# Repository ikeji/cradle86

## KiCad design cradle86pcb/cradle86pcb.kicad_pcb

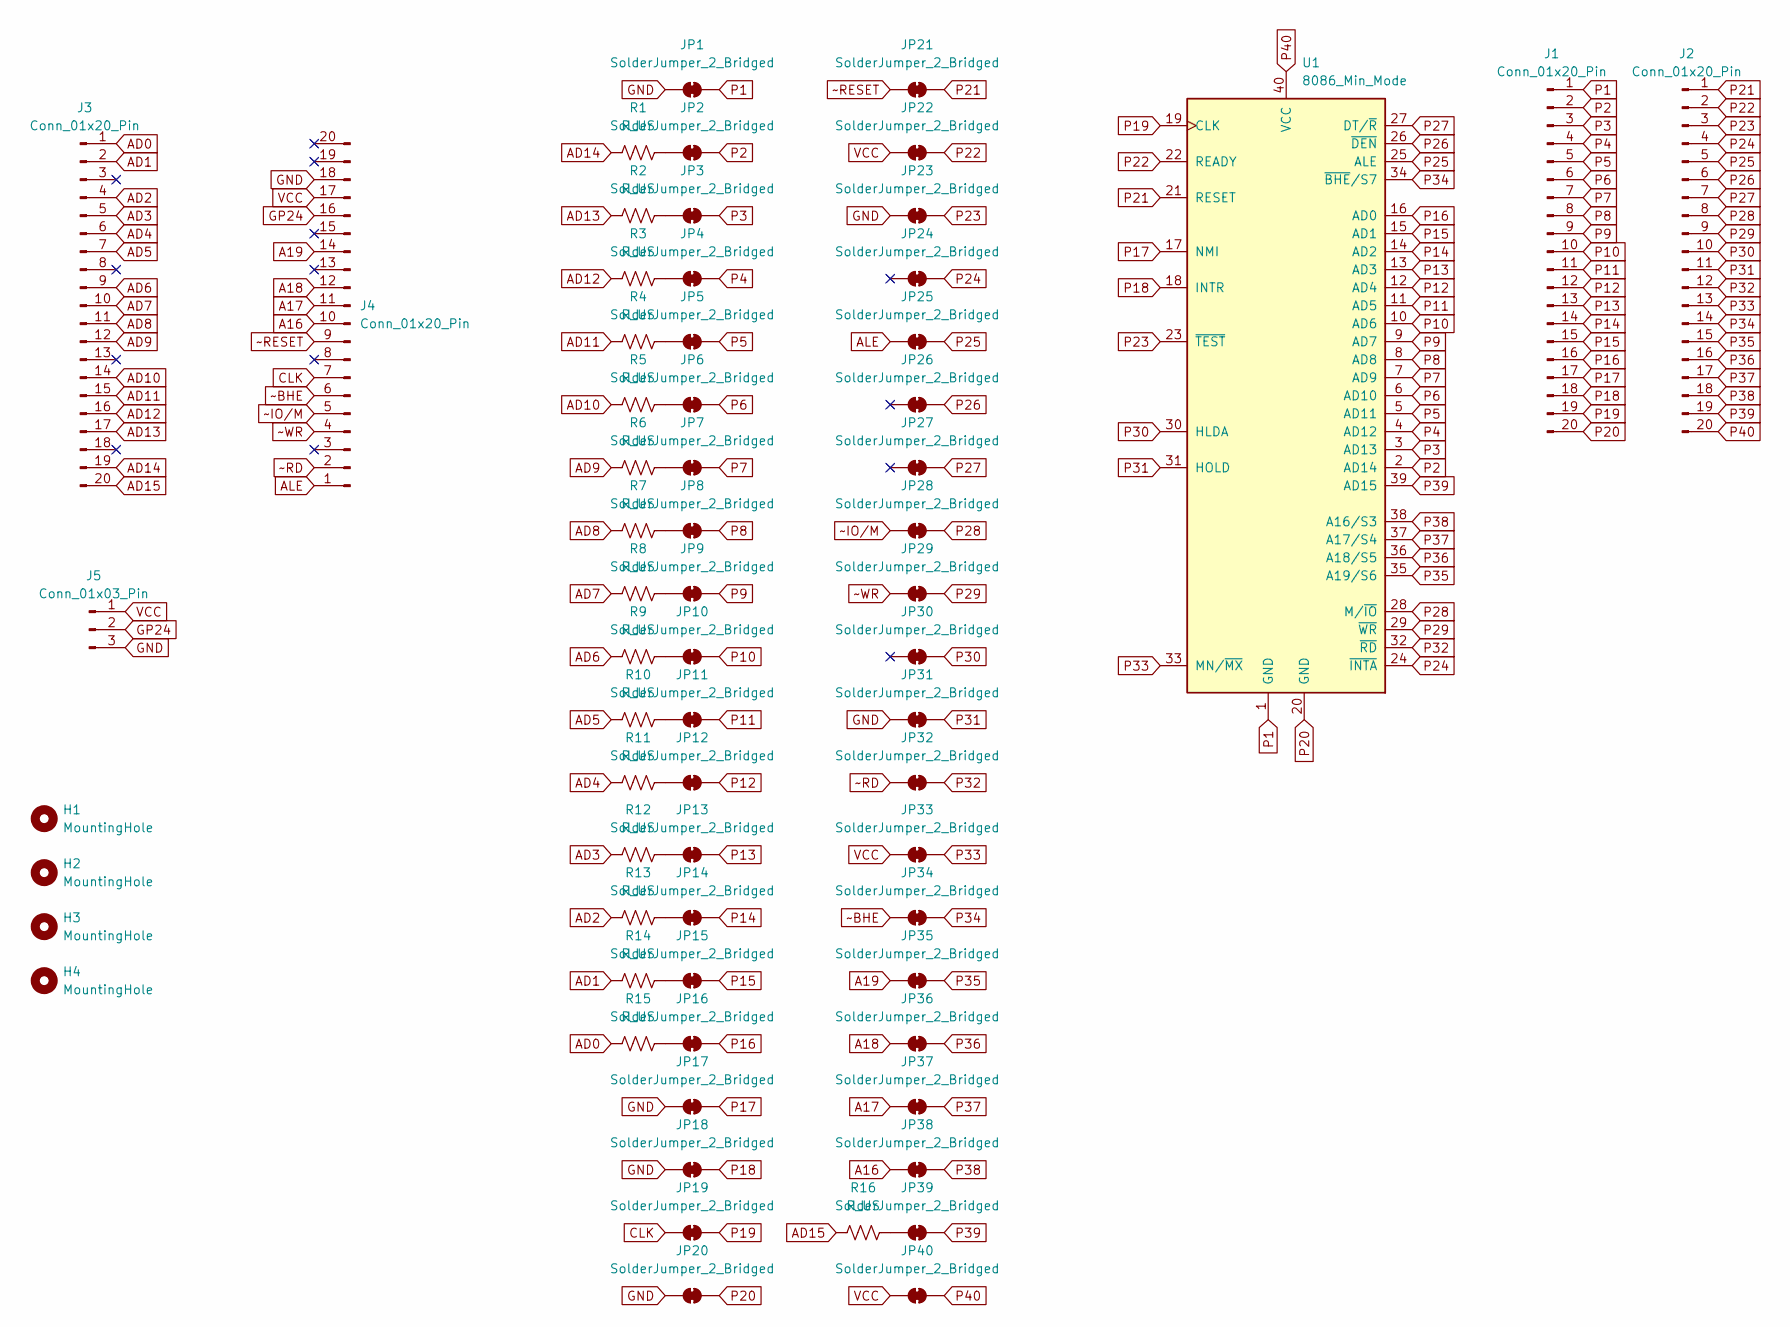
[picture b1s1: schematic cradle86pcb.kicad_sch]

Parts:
H1, H2, H3, H4: MountingHole; MountingHole_3.2mm_M3
J1, J2, J3, J4: Conn_01x20_Pin; PinHeader_1x20_P2.54mm_Vertical
J5: Conn_01x03_Pin; PinHeader_1x03_P2.54mm_Vertical
JP1, JP2, JP3, JP4, JP5, JP6, JP7, JP8, JP9, JP10, JP11, JP12, JP13, JP14, JP15, JP16, JP17, JP18, JP19, JP20, JP21, JP22, JP23, JP24, JP25, JP26, JP27, JP28, JP29, JP30, JP31, JP32, JP33, JP34, JP35, JP36, JP37, JP38, JP39, JP40: SolderJumper_2_Bridged; SolderJumper-2_P1.3mm_Bridged_Pad1.0x1.5mm
R1, R2, R3, R4, R5, R6, R7, R8, R9, R10, R11, R12, R13, R14, R15, R16: R_US; R_Axial_DIN0207_L6.3mm_D2.5mm_P10.16mm_Horizontal
U1: 8086_Min_Mode; DIP-40_W15.24mm

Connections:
A16: J4.10, JP38.1 (A)
A17: J4.11, JP37.1 (A)
A18: J4.12, JP36.1 (A)
A19: J4.14, JP35.1 (A)
AD0: J3.1, R15.1
AD1: J3.2, R14.1
AD2: J3.4, R13.1
AD3: J3.5, R12.1
AD4: J3.6, R11.1
AD5: J3.7, R10.1
AD6: J3.9, R9.1
AD7: J3.10, R8.1
AD8: J3.11, R7.1
AD9: J3.12, R6.1
AD10: J3.14, R5.1
AD11: J3.15, R4.1
AD12: J3.16, R3.1
AD13: J3.17, R2.1
AD14: J3.19, R1.1
AD15: J3.20, R16.1
ALE: J4.1, JP25.1 (A)
CLK: J4.7, JP19.1 (A)
GND: J4.18, J5.3, JP1.1 (A), JP17.1 (A), JP18.1 (A), JP20.1 (A), JP23.1 (A), JP31.1 (A)
GP24: J4.16, J5.2
unnamed: JP2.1 (A), R1.2
unnamed: JP3.1 (A), R2.2
unnamed: JP4.1 (A), R3.2
unnamed: JP5.1 (A), R4.2
unnamed: JP6.1 (A), R5.2
unnamed: JP7.1 (A), R6.2
unnamed: JP8.1 (A), R7.2
unnamed: JP9.1 (A), R8.2
unnamed: JP10.1 (A), R9.2
unnamed: JP11.1 (A), R10.2
unnamed: JP12.1 (A), R11.2
unnamed: JP13.1 (A), R12.2
unnamed: JP14.1 (A), R13.2
unnamed: JP15.1 (A), R14.2
unnamed: JP16.1 (A), R15.2
unnamed: JP39.1 (A), R16.2
P1: J1.1, JP1.2 (B), U1.1 (GND)
P2: J1.2, JP2.2 (B), U1.2 (AD14)
P3: J1.3, JP3.2 (B), U1.3 (AD13)
P4: J1.4, JP4.2 (B), U1.4 (AD12)
P5: J1.5, JP5.2 (B), U1.5 (AD11)
P6: J1.6, JP6.2 (B), U1.6 (AD10)
P7: J1.7, JP7.2 (B), U1.7 (AD9)
P8: J1.8, JP8.2 (B), U1.8 (AD8)
P9: J1.9, JP9.2 (B), U1.9 (AD7)
P10: J1.10, JP10.2 (B), U1.10 (AD6)
P11: J1.11, JP11.2 (B), U1.11 (AD5)
P12: J1.12, JP12.2 (B), U1.12 (AD4)
P13: J1.13, JP13.2 (B), U1.13 (AD3)
P14: J1.14, JP14.2 (B), U1.14 (AD2)
P15: J1.15, JP15.2 (B), U1.15 (AD1)
P16: J1.16, JP16.2 (B), U1.16 (AD0)
P17: J1.17, JP17.2 (B), U1.17 (NMI)
P18: J1.18, JP18.2 (B), U1.18 (INTR)
P19: J1.19, JP19.2 (B), U1.19 (CLK)
P20: J1.20, JP20.2 (B), U1.20 (GND)
P21: J2.1, JP21.2 (B), U1.21 (RESET)
P22: J2.2, JP22.2 (B), U1.22 (READY)
P23: J2.3, JP23.2 (B), U1.23 (~TEST)
P24: J2.4, JP24.2 (B), U1.24 (~INTA)
P25: J2.5, JP25.2 (B), U1.25 (ALE)
P26: J2.6, JP26.2 (B), U1.26 (~DEN)
P27: J2.7, JP27.2 (B), U1.27 (DT/~R)
P28: J2.8, JP28.2 (B), U1.28 (M/~IO)
P29: J2.9, JP29.2 (B), U1.29 (~WR)
P30: J2.10, JP30.2 (B), U1.30 (HLDA)
P31: J2.11, JP31.2 (B), U1.31 (HOLD)
P32: J2.12, JP32.2 (B), U1.32 (~RD)
P33: J2.13, JP33.2 (B), U1.33 (MN/~MX)
P34: J2.14, JP34.2 (B), U1.34 (~BHE/S7)
P35: J2.15, JP35.2 (B), U1.35 (A19/S6)
P36: J2.16, JP36.2 (B), U1.36 (A18/S5)
P37: J2.17, JP37.2 (B), U1.37 (A17/S4)
P38: J2.18, JP38.2 (B), U1.38 (A16/S3)
P39: J2.19, JP39.2 (B), U1.39 (AD15)
P40: J2.20, JP40.2 (B), U1.40 (VCC)
VCC: J4.17, J5.1, JP22.1 (A), JP33.1 (A), JP40.1 (A)
~BHE: J4.6, JP34.1 (A)
~IO/M: J4.5, JP28.1 (A)
~RD: J4.2, JP32.1 (A)
~RESET: J4.9, JP21.1 (A)
~WR: J4.4, JP29.1 (A)

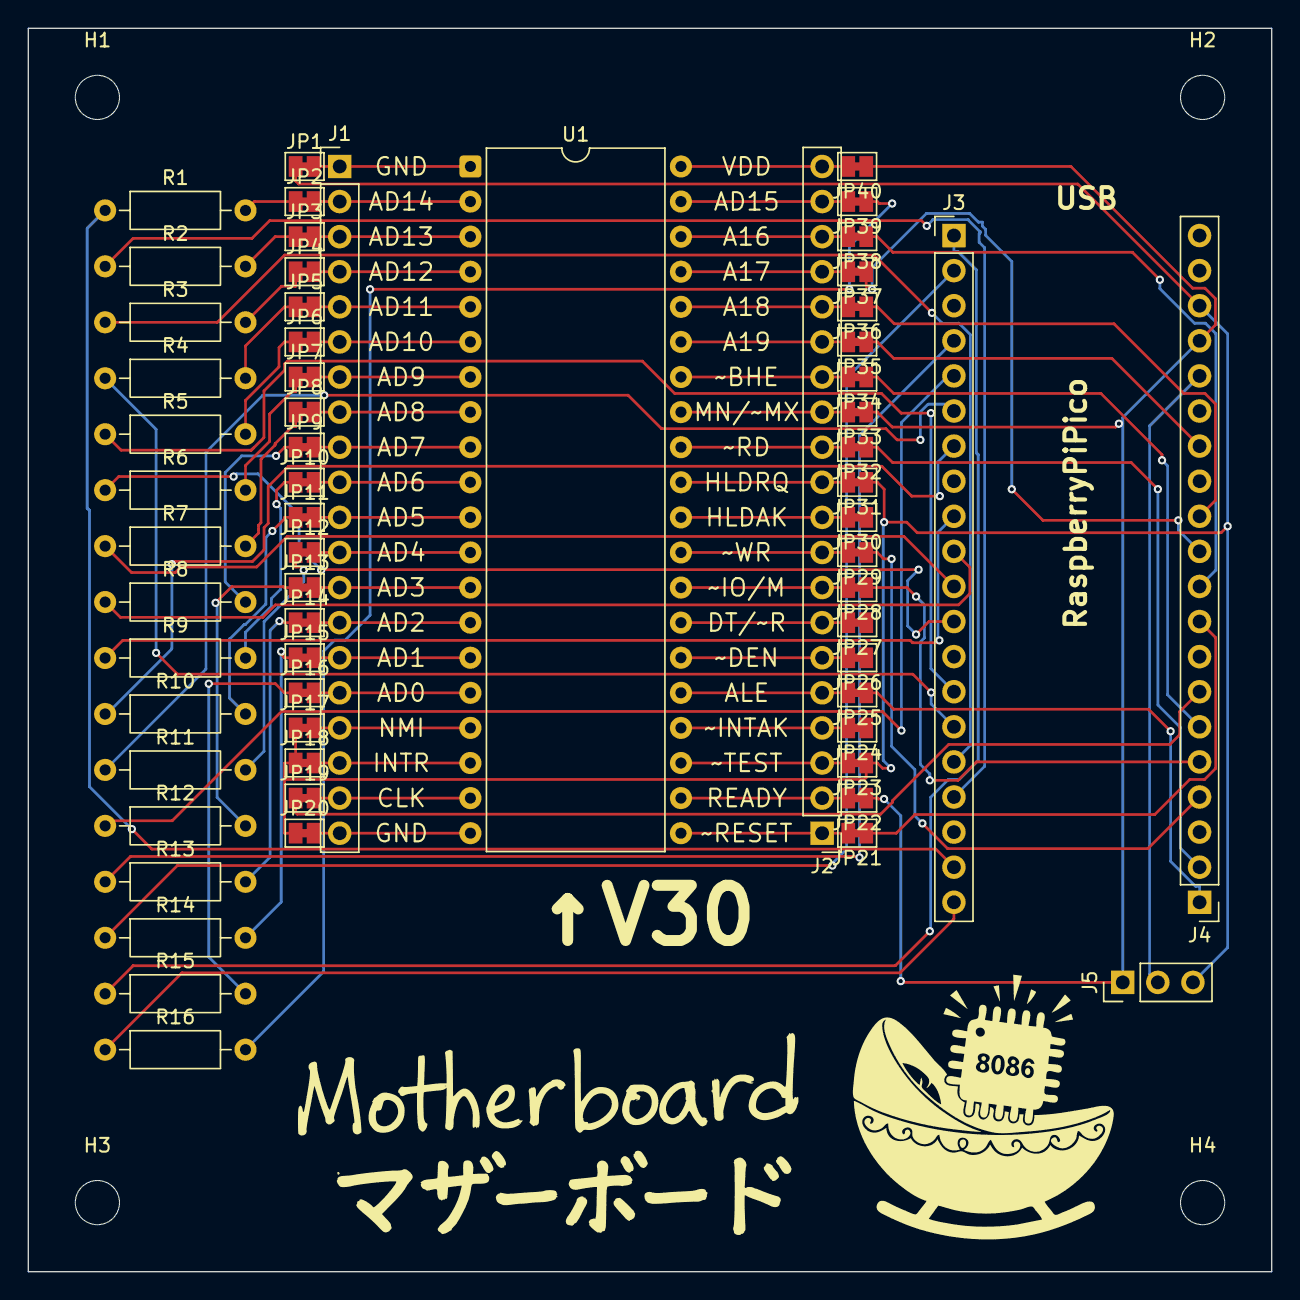
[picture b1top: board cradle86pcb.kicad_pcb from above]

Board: 2 copper layers, 90.0 x 90.0 mm, 66 parts (0 on the bottom side), 86 nets.

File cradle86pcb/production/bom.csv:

Designator,Footprint,Quantity,Value,LCSC Part #
"J1, J2, J3, J4",PinHeader_1x20_P2.54mm_Vertical,4,Conn_01x20_Pin,
J5,PinHeader_1x03_P2.54mm_Vertical,1,Conn_01x03_Pin,
"R1, R10, R11, R12, R13, R14, R15, R16, R2, R3, R4, R5, R6, R7, R8, R9",R_Axial_DIN0207_L6.3mm_D2.5mm_P10.16mm_Horizontal,16,R_US,
U1,DIP-40_W15.24mm,1,8086_Min_Mode,

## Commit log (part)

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2025-11-21 feat: KiCad PCBデザインの初期コミット
    cradle86pcbプロジェクトのKiCad PCBデザインファイルを追加。
    生成されるバックアップファイルやログファイルを無視するための.gitignoreを追加。
2025-11-25 feat: PicoとV30接続に関する設計と開発ワークフローの議論
    Raspberry Pi PicoとNEC V30 CPUの接続に関する詳細な設計議論を記録。
    V30をミニマムモードで動作させ、Picoの限られたGPIOを最大限活用するためのピン配置戦略を提案。
    V30の全40ピンに対する詳細な接続テーブル、3.3V/5Vの電圧レベル変換（レベルシフタや直列抵抗）の必要性について解説。
    Pico C/C++ SDKを用いたV30バス制御ソフトウェアのアーキテクチャ、マルチプレクスバス処理、デュアルコア運用によるUSB通信とバス制御の分離を説明。
    Pico互換機のオンボードLED・ス
2025-11-25 feat: PWMクロック生成とコマンド引数解析の修正
    PWM機能を使用してPIN_CLK_OUTに4MHzのクロックを生成するように変更しました。これにより、より柔軟なクロック制御が可能になります。
    コマンド引数（cmd_dump, cmd_edit）の解析において、strtokが入力文字列を変更する問題に対処するため、引数のコピーを使用するように修正しました。これにより、コマンドの堅牢性が向上します。
    Pico SDKのインポート方法を標準化し、PICO_SDK_PATHをMakefileで設定可能にし、CMakeに渡すようにビルドシステムを改善しました。
    PIN_A17、PIN_A18、PIN_A1
2025-11-25 ``` chore: .gitignoreファイルの追加
    一般的なビルド生成物、エディタの一時ファイル、OS固有のファイル、およびPython関連のファイルを無視するように設定しました。
    これにより、不要なファイルがリポジトリに含まれるのを防ぎ、クリーンなバージョン管理を促進します。
    ```
2025-11-25 feat: V30バスドライバに動的なクロック周波数設定機能を追加
    V30バスドライバに動的なクロック周波数設定機能が追加されました。
    `FreqSetting`構造体と`freq_table`配列を導入し、サポートされるクロック周波数とそのPWM設定値（wrap、div）を定義しました。
    新しい`setup_clock`関数は、指定された周波数に基づいて`PIN_CLK_OUT`のPWMを構成し、クロックを生成します。設定中にグリッチを防ぐロジックと、サポートされていない周波数に対するエラー処理も含まれています。
    CLIに`c <kHz>`コマンドが追加され、ユーザーがリアルタイ
2025-11-25 Fix: PicoフラッシングのMakefileを更新
    デフォルトのMOUNT_DEVICEを`/dev/sdb1`から`/dev/sda1`に変更し、幅広い互換性に対応しました。
    MOUNT_POINTを`/mnt/pico`から`$(HOME)/mnt/pico`に変更し、ルート権限なしでディレクトリ作成/アクセスを可能にしました。
    `mount`コマンドに`-o uid=id -u`オプションを追加し、マウントされたデバイスが現在のユーザーによって所有されるようにすることで、フラッシング中の潜在的な権限問題を解決しました。
2025-11-26 feat: アセンブラと逆アセンブラの機能強化、およびMakefileの改善
    アセンブラに`db`命令と遠方ジャンプ(`jmp segment:offset`)のサポートを追加しました。これにより、より柔軟なコード記述が可能になります。即値とメモリアドレスの解釈を16進数に統一し、8ビットレジスタの利用に対応しました。
    逆アセンブラには、`mov reg8, imm8`、`add al, imm8`、`mov [imm16], al`、遠方ジャンプ、`hlt`命令の表示機能を追加し、デバッグ時の可読性を向上させました。
    MakefileにはXMODEM転送用の`test-flash`ターゲットが追加され、バイナリの書き込み
2025-11-26 ``` docs: 主要関数に日本語コメントを追加
    V30ハードウェア操作、XMODEMプロトコル、およびCLIモニターコマンドに関連する主要なC++関数に、詳細な日本語コメントを追加しました。
    これにより、コードの可読性と保守性が向上し、各関数の目的、引数、および戻り値が明確になります。
    具体的には、バス方向設定、アドレス読み取り、データ書き込み、アドレスマッピング、クロック設定、Core 1処理、XMODEM送受信、メモリダンプ、編集、逆アセンブル、レジスタ変換、およびメイン関数のコメントを更新しました。
    ```
2025-11-28 feat: XMODEM通信の信頼性向上と自動テストフローの改善
    XMODEM送受信関数の堅牢性を大幅に向上させ、エラー処理、リトライメカニズム、バッファオーバーフロー保護を強化した。
    自動テストのワークフローを改善し、Picoとホスト間の同期を密にした。
    MakefileのMOUNT_DEVICE定義を、より安定したUSBデバイスIDベースのパスに更新した。
    シリアル通信のCRLF変換を無効化し、バイナリ転送の整合性を確保。
    バージョン文字列を`0.0.1`にリセットした。
2025-11-28 feat: XMODEMによるRAMダンプ取得機能を追加
    デバイスからXMODEMを介してRAMダンプを取得する`test-retrieve`ターゲットをMakefileに追加しました。
    XMODEMでのデータ送信開始を自動化するexpectスクリプト`run-xs.exp`を新規作成しました。
    生成されるダンプファイル`dump.bin`がリポジトリに含まれないよう、.gitignoreに追加しました。
2025-11-28 feat: C言語テスト環境の追加とリセットベクタの統合
    V30 (8086) プロセッサ向けのC言語テストをサポートするため、ビルドシステムとテストランナーを拡張しました。
    Makefileを更新し、bccコンパイラとld86リンカを使用してCソースコード (test-c.c) をコンパイルし、リセットベクタ (reset_vec.bin) を含む64KBの実行可能バイナリ (test-c.bin) を生成するルールを追加しました。
    reset_vec.asmを新規作成し、ブート時のプログラム開始アドレス (0x0000:0x0000) へのジャンプを実装しました。test-c.cでは、_start関数内でスタックポインタを0x8000
2025-11-30 feat: メモリフィルとサイクル指定実行コマンドを実装
    新しい`f` (fill) コマンドを追加し、指定されたバイト値 (デフォルトは0xF4) で全メモリを埋める機能を提供。
    `r` (run) コマンドを拡張し、オプションでCPUサイクル数を指定して実行できるようにした。
    core1のコマンド解析をリファクタリングし、下位2ビットでコマンドタイプ、残りのビットでサイクル制限を表現するように変更。これにより将来のコマンド拡張が容易になる。
    デフォルトのRAM初期化値を0x90から0xF4に変更し、新しいフィルコマンドのデフォルト値と
2025-12-01 feat(core1): バスサイクル監視の安定性向上と初期化処理の追加
    Core1エントリポイントでAD0-15をGPIOとして初期化する処理を追加。
    RESETピンの初期状態をリセット解除（高レベル）に修正。
    ALE信号検出およびRD/WR信号待機処理にタイムアウトを導入し、ハングアップを防止。
    RD信号検出時に3usの遅延を追加し、バス通信の安定性を向上。
    バスサイクル中にALEが予期せず検出された場合の処理を追加し、同期問題を軽減。
    CMD_LOG_RUNコマンドにMAX_CYCLESを渡し、実行サイクル制限を動的に設定できるように変更。
2025-12-05 feat: 8086メモリアクセスロジックを正確化、ドキュメントとログを改善
    `main.cpp`にて、V30 CPUのメモリアクセス処理を8086バスサイクルの仕様に厳密に準拠するよう改修。
    メモリ読み出しは、常にワードアラインされたデータをPicoのRAMから読み出し、CPU側でA0とBHE#に基づいてバイト選択を行う最適化された方式に変更。
    メモリ書き込みは、A0とBHE#信号の組み合わせに応じたワード/上位バイト/下位バイト書き込みロジックを正確に実装。
    `memaccess.md`を追加し、8086のメモリアクセス原理およびPicoでの実装アルゴリズムに関す
2025-12-06 feat: I/O専用ロギング機能を追加し、ログ記録ロジックを改善
    V30バスモニターにI/Oアクセスのみを記録する新しいロギングモード（CMD_IOLOG_RUN）を追加しました。これにより、特定のI/O操作のデバッグと分析が容易になります。
    変更点：
    - `CMD_IOLOG_RUN` コマンドを導入し、CLIの `i` コマンドで呼び出せるようにしました。
    - ロギングロジックを再構築し、`bus_cycles`で実際のバスサイクル数を追跡し、`logged_cycles`で記録されたエントリ数を管理するようにしました。
    - `CMD_LOG_RUN`（`r` コマンド）は全てのバスサイクルを記録し
2025-12-06 feat: V30実行コマンドを改善し、無限サイクル実行とロギングモードを統一
    Core 1コマンドをenumにリファクタリングし、ロギングモードの管理を簡素化しました。
    `r`および`i`コマンドに無限サイクル実行オプションを追加しました。引数を省略するか、0を指定することで、キー入力による停止までV30を実行できるようになります。
    `g`コマンドも同様に無限サイクル実行として動作し、停止時に実行されたサイクル数を表示するようにしました。
    `core1_entry`における実行ループの終了条件を統一し、より堅牢な動作を実現し
2025-12-06 feat: autotestコマンドにI/Oログモードを追加
    monitorのautotestコマンドにオプションの`io`引数を追加し、詳細なフルログモードと簡潔なI/Oログモードを切り替えられるようにしました。
    これにより、テスト実行時のログ出力量を制御し、デバッグや分析の効率を向上させます。
    変更点:
    - `monitor/main.cpp`: `autotest`コマンドが`io`引数を受け入れ、ログモードを`CMD_RUN_IOLOG`または`CMD_RUN_FULLLOG`に設定するように更新しました。
    - `monitor/Makefile`: `run-c`および`run`ターゲットがデフォルトでフルログモードを使用するように明示し、I/Oロ
2025-12-06 feat: freq_tableに新しい周波数設定を追加
    monitor/main.cppのfreq_tableに周波数設定を追加しました。
    これにより、より多様な周波数オプションが利用可能になります。
    具体的には、750kHz、500kHz、250kHzの周波数設定が追加されました。
2025-12-06 test: ディレイ関数を追加し、その出力をテスト
    test-c.cに新しいディレイ関数`delay()`を追加しました。
    この関数は、簡単なループを実行して擬似的な遅延を生成し、その結果を返します。
    `main`関数内で`delay()`を呼び出し、その戻り値を`out()`関数で出力することで、この機能の動作を検証します。
2025-12-06 ``` build: セットアップターゲットをMakefileに追加
    開発環境の準備を容易にするため、`bcc`と`expect`パッケージをインストールする`setup`ターゲットをMakefileに追加しました。
    ```
2025-12-12 feat: COMMAND.COM動作のためのメモリイメージ設計書を追加
    8086 CPU上でCOMMAND.COMを動作させるための設計書`design.md`を追加しました。
    このドキュメントには、マシンの仕様（8086 CPU、128KB RAM、メモリマップ）、目標（COMMAND.COMの起動、内部コマンドの実行、モニターIO機能、割り込みハンドラの提供）、メモリマップの詳細、および実装戦略（128KBのバイナリファイル、NASM、ログスクリプト、Makefile）が記載されています。
    mini-DOS環境の初期メモリ設定と計画されている機能の概要を説明します。
2025-12-13 feat: ブートローダとOS起動メカニズムを実装し、COMMAND.COMを実行可能に
    新しいブートローダ `boot.asm` を導入し、BIOSによる起動シーケンスを確立。ブートローダは自身を退避後、ディスクから `mini-dos.img` (OSカーネルとCOMMAND.COMを含む) をメモリの `0x00000` へロードします。
    `main.asm` をOSのメインエントリポイントとして追加し、`COMMAND.COM` を物理アドレス `0x1100` に組み込みます。これにより、`COMMAND.COM` の実行に必要な初期環境（スタック、PSP、IVT）が設定され、基本的なDOS API (`INT 21h` の文字出力、バージョン取得、プログ
2025-12-14 test: COM1テストブートセクタの追加
    COM1シリアルポートからの「Hello World」出力テストのため、PC-XT互換ブートセクタを追加しました。
    `boot.asm`は、シリアルポート(0x3F8)経由で文字列を送信し、QEMUの`isa-debug-exit`デバイスを使用して終了します。
    `Makefile`はNASMで`boot.asm`をアセンブルし、QEMUで実行するためのターゲットを提供します。
    また、Bochsでのテスト用に`bochs.cfg`も追加されました。
2025-12-14 feat: QEMUログのデコード機能を追加し、アセンブリロギングを改善
    `boot.asm`の`log_char`マクロと`print_al_char`サブルーチンにレジスタの保存・復元処理を追加し、堅牢性を高めました。
    QEMUログの出力形式を単一文字のログコードに変更し、`run-qemu.sh`スクリプトが`log_parser.py`を介してこれらのコードを人間が読めるメッセージにデコードするように更新しました。
    `log_parser.py`には、ログコードとその意味をマッピングする`DECODE_MAP`が導入され、QEMU実行時のデバッグ情報が格段に理解しやすくなりました。
2025-12-14 feat: ブートローダーのスタック初期化とデバッグログを追加
    ブートローダーがセグメントレジスタとスタックポインタを早期に、かつリロケーション後も適切に初期化するように改善。
    BIOSから渡されるブートドライブ番号と、ブートローダーのスタックセグメントレジスタの値をログに出力する機能を追加。
    対応するログ解析用マッピングをlog_parser.pyに追加し、デバッグ時の可読性を向上。
2025-12-14 chore: Add build artifacts and log files to .gitignore
2025-12-14 feat: ブートローダーのデバッグログを改善
    ブートローダーのディスク操作に関するデバッグログを強化しました。
    `int 0x13` 呼び出し後の `AL` レジスタと `AH` レジスタの内容を記録することで、
    ディスクリセット、ステータスチェック、セクター読み込み時のエラー情報を詳細に追跡できるようになりました。
    これに伴い、`boot.asm` 内のロギング文字が更新され、`tools/log_parser.py` も
    新しいログマップに対応するように修正されています。
    `run-qemu.sh` の待機時間もデバッグ効率向上のため短縮されました。
2025-12-14 feat: 拡張BIOSディスク読み込み機能とメモリダンプマクロを導入
    ブートローダーのディスク読み込みメカニズムを更新しました。
    従来のINT 13h AH=02hから、Disk Address Packet (DAP) を使用する拡張INT 13h AH=42hに移行。
    これにより、LBA（論理ブロックアドレス）指定によるセクター読み込みが可能になり、より柔軟なディスクアクセスを実現します。
    具体的には、LBA 1から始まる128セクターをメモリアドレス0x8000:0x0000にロードするように変更しました。
    また、デバッグを容易にするため、指定されたメモリ範囲の内容を16進数で
2025-12-15 ``` feat: カーネル起動処理の改善と汎用割り込みハンドラの導入
    Interrupt Vector Table (IVT) を初期化し、全ての割り込みエントリを設定しました。
    256個の汎用割り込みサービスルーチン (ISR) を作成し、割り込み発生時にCOM1へデバッグメッセージを出力するようにしました。
    ブートシーケンスを修正し、初期化後に `COMMAND.COM` へ制御を移行するように変更しました。
    COM1への16進数出力機能を追加し、デバッグを容易にしました。
    ```
2025-12-15 feat: INT 21hハンドリングを拡張し、割り込みを有効化
    COMMAND.COM起動前に割り込みを有効化する `sti` 命令を追加し、OSの応答性を向上。
    INT 21hハンドラを拡張し、AH=02h (文字表示) と AH=50h (PSP設定) をサポート。
    `current_psp`変数を導入し、INT 21hからの戻り時にキャリーフラグをクリアするよう修正。
2025-12-16 feat: mini-dos実行ターゲットとモニタリング機能の改善
    monitor/Makefileに`run-mini-dos`ターゲットを追加しました。これにより、`../mini-dos/mini-dos.img`をI/Oログモードで実行できるようになります。
    monitor/main.cppにて、仮想RAMサイズを64KB (0x10000) から128KB (0x20000) に拡張しました。
    monitor/test_runner.pyのログ出力表示を改善し、バイトアクセス時（HIGH_BYTE, LOW_BYTE）に32〜126の範囲内の値であれば、そのASCII文字も表示するようにしました。また、これに伴いログテーブルの幅を調整しました。
2025-12-17 feat: 割り込みハンドリングにカーネルスタックを実装し、モニタの実行モードを更新
    main.asm: 割り込みサービスルーチン (ISR) のハンドリングにカーネルスタックを導入しました。これにより、ユーザーのスタックを保存し、カーネル独自のスタックに切り替えてから割り込みを処理し、リターン前にユーザーのスタックを復元します。これはシステム安定性を向上させ、ユーザーのスタックを破壊することなく、より複雑なカーネル操作を可能にします。また、ISR開始時に割り込みを無効化 (cl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
2025-12-18 feat: INT 21hの文字列表示、メモリ管理、およびインメモリCOMMAND.COMサポートを実装
    AH=09h (文字列表示), AH=48h (メモリ割り当て), AH=4Ah (メモリブロックサイズ変更) のINT 21hサービスを実装しました。
    COMMAND.COMをカーネル内に埋め込み、ファイルハンドル42に対するINT 21h (ファイル読み込み: AH=3Fh, シーク: AH=42h) がこのインメモリCOMMAND.COMを操作できるようにしました。
    QEMU実行スクリプトを更新し、COM2出力をqemu2.logに保存するようにしました。
    isr.mdを更新し、新しいINT 21h機能について記述しました。
2025-12-20 feat: INT 21h, AH=25h (割り込みベクタ設定) の実装
    INT 21h の AH=25h サブファンクションを実装し、指定された割り込み番号のベクタを設定できるようにしました。
    割り込み番号、新しいハンドラのセグメントとオフセットをIVTに書き込む処理を追加しました。
    デバッグと監視のため、設定される割り込み番号 (AL)、セグメント (DS)、オフセット (DX) の値をCOM1にログ出力する機能を含めました。
    関連するドキュメント (isr.md) を更新し、この新しい機能について記述しました。
2025-12-20 ``` feat: INT 21h, AH=0Ah (バッファ付き入力) の実装
    INT 21h, AH=0Ah (バッファ付き入力) のサポートを追加しました。
    この機能は、COM1にDS:DXの値をログ出力し、内部状態に基づいて「u」または「r」のいずれかの文字列をユーザーの指定するバッファに書き込みます。
    応答は呼び出しごとに「u」と「r」が循環的に切り替わります。
    isr.mdにも関連する説明を追記しました。
    ```
2025-12-23 ``` feat: 初期ブートイメージ作成セットアップ
    組み込みHiDOSのブートイメージ作成に関する初期セットアップを実装。
    以下の変更が含まれます:
    - `boot.img` (128KB) を生成する `Makefile` を追加。`VM_IO.SYS` と `MSDOS.SYS` を指定されたメモリアドレスに配置し、ブートジャンプ、割り込みハンドラ (INT 86h)、割り込みベクタを設定します。
    - バイナリファイル `VM_IO.SYS` と `MSDOS.SYS` を追加。
    - 生成されるイメージファイルを無視するための `.gitignore` を追加。
    - ブートイメージ作成の要件を記載した `idea.md` を追加。
2025-12-25 feat: ケースの寸法調整と基板固定構造の追加
    ケースの外形高と蓋の厚みを調整し、全体の寸法を見直しました。
    基板を固定するための台座と突起を追加し、内部構造を改善しました。
    ノッチの名称をトップノッチに変更しました。
2025-12-25 feat: HIDOS VMのI/O処理を実装
    Core 1にHIDOS VMのI/O処理をエミュレートする機能を追加しました。
    `0x86`番地へのI/Oアクセスを捕捉し、仮想デバイス（コンソール、ディスク、補助ポートなど）への処理をディスパッチします。
    これに伴い、メモリリード/ライトヘルパー関数（`memr2`, `memw2`等）も定義しました。
    また、デフォルトのクロック周波数を500kHzから125kHzに調整しています。
2025-12-25 feat: VMに組み込みディスクイメージ機能を追加
    HIDOS VMが利用できる組み込みディスクイメージ機能を追加しました。
    `CMakeLists.txt`を更新し、`../embedded-hidos/disk.img`をバイナリとしてコンパイルし、実行ファイルに含めるようにしました。
    `main.cpp`では、`_binary_disk_img_start`などのシンボルを使ってディスクイメージにアクセスし、VMのI/Oハンドラを通じてディスク読み取り操作をサポートします。
    これにより、VMはホスト側のファイルシステムに依存せず、内蔵のディスクイメージからデータをロードできるようになります。
2025-12-26 ``` feat: Makefile: MSDOS.SYSのオフセットを固定値に修正
    VM_IO.SYSのサイズに基づいて動的に計算されていたMSDOS_OFFSETを、
    固定値98304 (0x18000) に変更しました。
    これにより、MS-DOSイメージの配置が安定し、特定のビルドシナリオで
    一貫性が確保されます。
    ```
2025-12-27 feat: boot.imgロード機能とBOOTSELリブート機能を追加
    `monitor`に`boot.img`をエミュレートされたRAMへロードする機能を追加しました。
    `boot.img`はバイナリとして実行可能ファイルに埋め込まれ、新しい`k`コマンドでロードできます。
    また、Raspberry Pi PicoをBOOTSELモードで再起動する`b`コマンドを追加しました。
    これらの機能により、開発中のシステムのテストとデバッグが容易になります。
2025-12-28 feat: モニタのコンソール入力処理を堅牢化
    RPおよびR1コマンドにおいて、getchar_timeout_us(0)を使用した非ブロッキング読み取りと、入力文字を一時的に保持するバッファ（last変数）の仕組みを導入しました。これにより、文字が利用可能になった場合にのみ取得し、ポーリングの効率を向上させます。
    RWコマンドでは、getchar_timeout_us(10000)を用いたタイムアウト付きのブロッキング読み取りを実装しました。これにより、アイドル状態でのCPU使用率を低減しつつ、入力された文字を内部バッファに保持することが可能になり
2026-02-04 feat: HIDOSサブモジュールを追加
    HIDOSプロジェクトをサブモジュールとして追加しました。
    これにより、cradle86プロジェクト内でHIDOSのバージョン管理が容易になります。
    HIDOSは`git@github.com:ikeji/HIDOS.git`から参照されます。
2026-02-04 refactor: HIDOS関連の命名とビルド依存関係を改善
    hidosvm関連のコードをhidos_cpuにリファクタリングし、命名を統一しました。
    Makefileでembedded-hidosのビルド依存関係を明示的に追加しました。
    core1のCPUリセットロジックを調整し、HIDOS起動時にも適切にリセットが適用されるようにしました。
